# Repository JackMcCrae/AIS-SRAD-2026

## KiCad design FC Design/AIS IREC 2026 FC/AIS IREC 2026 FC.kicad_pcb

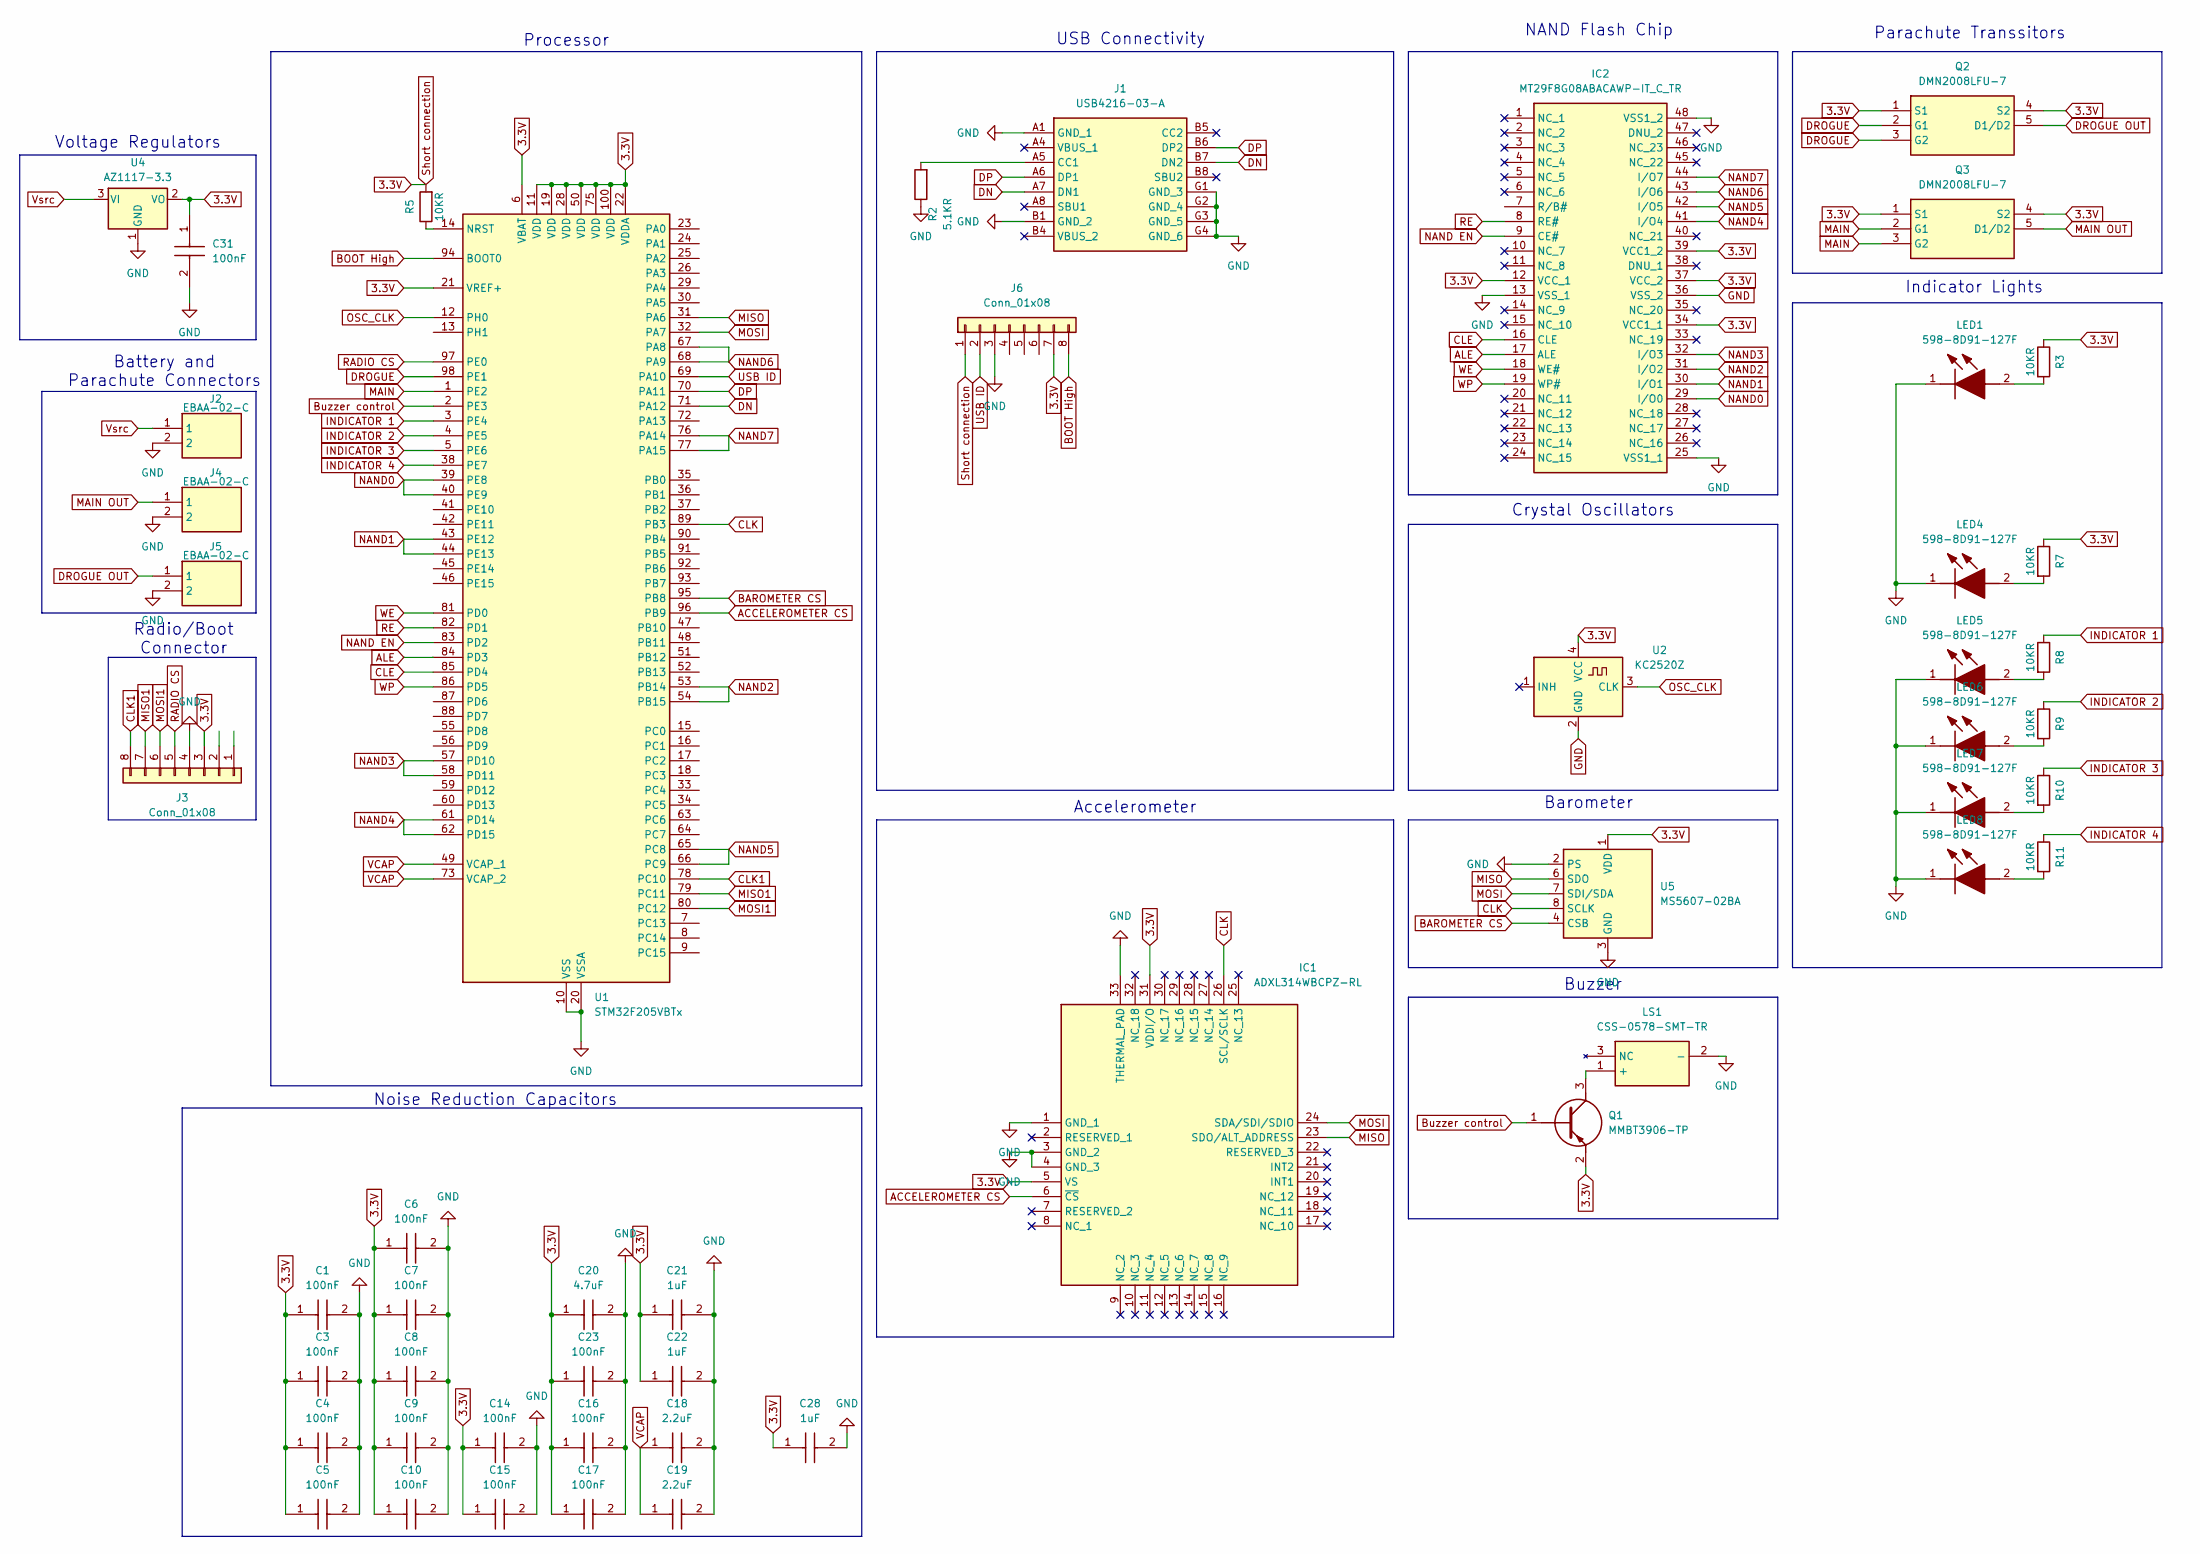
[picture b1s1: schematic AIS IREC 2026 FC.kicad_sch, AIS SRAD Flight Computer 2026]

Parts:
C1, C3, C4, C5, C6, C7, C8, C9, C10, C14, C15, C16, C17, C23, C31: 100nF; GRM022C81C222KE01L; Mouser Part Number 81-GRM022R61A104KE1L
C18, C19: 2.2uF; GRM033D70J224ME01D; Mouser Part Number 81-GRM033R61A225KE7D
C20: 4.7uF; GRM033D70J224ME01D; Mouser Part Number 81-GRM035R60J475ME5D
C21, C22, C28: 1uF; CAPC0603X33N; Mouser Part Number 81-GRT033R60J105ME3D
IC1: ADXL314WBCPZ-RL; QFN50P500X500X155-33N-D; Mouser Part Number 584-ADXL314WBCPZ-RL
IC2: MT29F8G08ABACAWP-IT_C_TR; SOP50P2000X120-48N; Mouser Part Number 340-122942-REEL
J1: USB4216-03-A; USB421603A; Mouser Part Number 640-USB4216-03-A
J2, J4, J5: EBAA-02-C; EBAA02C; Mouser Part Number 737-EBAA-02-C
J3, J6: Conn_01x08; Hirose_DF13-08P-1.25DSA_1x08_P1.25mm_Vertical
LED1, LED4, LED5, LED6, LED7, LED8: 598-8D91-127F; 5988D91127F; Manufacturer_Part_Number 598-8D91-127F
LS1: CSS-0578-SMT-TR; CSS0578SMTTR; Mouser Part Number 490-CSS-0578-SMT-TR
Q1: MMBT3906-TP; SOT95P237X125-3N; Mouser Part Number 833-MMBT3906-TP
Q2, Q3: DMN2008LFU-7; DMN2008LFU7; Mouser Part Number 621-DMN2008LFU-7
R2: 5.1KR; R_0201_0603Metric
R3, R5, R7, R8, R9, R10, R11: 10KR; R_0201_0603Metric
U1: STM32F205VBTx; LQFP-100_14x14mm_P0.5mm
U2: KC2520Z; Oscillator_SMD_Kyocera_KC2520Z-4Pin_2.5x2.0mm
U4: AZ1117-3.3; SOT-223-3_TabPin2
U5: MS5607-02BA; LGA-8_3x5mm_P1.25mm

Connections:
3.3V: C1.1, C3.1, C4.1, C5.1, C6.1, C7.1, C8.1, C9.1, C10.1, C14.1, C15.1, C16.1, C17.1, C20.1, C21.1, C22.1, C23.1, C28.1, C31.1, IC1.5 (VS), IC1.31 (VDDI/O), IC2.12 (VCC_1), IC2.34 (VCC1_1), IC2.37 (VCC_2), IC2.39 (VCC1_2), J3.3, J6.1, J6.7, Q1.2 (E), Q2.1 (S1), Q2.4 (S2), Q3.1 (S1), Q3.4 (S2), R3.1, R5.2, R7.1, U1.6 (VBAT), U1.11 (VDD), U1.19 (VDD), U1.21 (VREF+), U1.22 (VDDA), U1.28 (VDD), U1.50 (VDD), U1.75 (VDD), U1.100 (VDD), U2.4 (VCC), U4.2 (VO), U5.1 (VDD)
ACCELEROMETER CS: IC1.6 (~CS), U1.96 (PB9)
ALE: IC2.17 (ALE), U1.84 (PD3)
BAROMETER CS: U1.95 (PB8), U5.4 (CSB), U5.5 (CSB)
BOOT High: J6.8, U1.94 (BOOT0)
Buzzer control: Q1.1 (B), U1.2 (PE3)
CLE: IC2.16 (CLE), U1.85 (PD4)
CLK: IC1.26 (SCL/SCLK), U1.89 (PB3), U5.8 (SCLK)
CLK1: J3.8, U1.78 (PC10)
DN: J1.A7 (DN1), J1.B7 (DN2), U1.71 (PA12)
DP: J1.A6 (DP1), J1.B6 (DP2), U1.70 (PA11)
DROGUE: Q2.2 (G1), Q2.3 (G2), U1.98 (PE1)
DROGUE OUT: J5.1, Q2.5 (D1/D2)
GND: C1.2, C3.2, C4.2, C5.2, C6.2, C7.2, C8.2, C9.2, C10.2, C14.2, C15.2, C16.2, C17.2, C18.2, C19.2, C20.2, C21.2, C22.2, C23.2, C28.2, C31.2, IC1.1 (GND_1), IC1.3 (GND_2), IC1.4 (GND_3), IC1.33 (THERMAL_PAD), IC2.13 (VSS_1), IC2.25 (VSS1_1), IC2.36 (VSS_2), IC2.48 (VSS1_2), J1.A1 (GND_1), J1.B1 (GND_2), J1.G1 (GND_3), J1.G2 (GND_4), J1.G3 (GND_5), J1.G4 (GND_6), J2.2, J3.4, J4.2, J5.2, J6.3, LED1.1 (K), LED4.1 (K), LED5.1 (K), LED6.1 (K), LED7.1 (K), LED8.1 (K), LS1.2 (-), R2.1, U1.10 (VSS), U1.20 (VSSA), U1.27 (VSS), U1.74 (VSS), U2.2 (GND), U4.1 (GND), U5.2 (PS), U5.3 (GND)
INDICATOR 1: R8.1, U1.3 (PE4)
INDICATOR 2: R9.1, U1.4 (PE5)
INDICATOR 3: R10.1, U1.5 (PE6)
INDICATOR 4: R11.1, U1.38 (PE7)
MAIN: Q3.2 (G1), Q3.3 (G2), U1.1 (PE2)
MAIN OUT: J4.1, Q3.5 (D1/D2)
MISO: IC1.23 (SDO/ALT_ADDRESS), U1.31 (PA6), U5.6 (SDO)
MISO1: J3.7, U1.79 (PC11)
MOSI: IC1.24 (SDA/SDI/SDIO), U1.32 (PA7), U5.7 (SDI/SDA)
MOSI1: J3.6, U1.80 (PC12)
NAND0: IC2.29 (I/O0), U1.39 (PE8), U1.40 (PE9)
NAND1: IC2.30 (I/O1), U1.43 (PE12), U1.44 (PE13)
NAND2: IC2.31 (I/O2), U1.53 (PB14), U1.54 (PB15)
NAND3: IC2.32 (I/O3), U1.57 (PD10), U1.58 (PD11)
NAND4: IC2.41 (I/O4), U1.61 (PD14), U1.62 (PD15)
NAND5: IC2.42 (I/O5), U1.65 (PC8), U1.66 (PC9)
NAND6: IC2.43 (I/O6), U1.67 (PA8), U1.68 (PA9)
NAND7: IC2.44 (I/O7), U1.76 (PA14), U1.77 (PA15)
NAND EN: IC2.9 (CE#), U1.83 (PD2)
unnamed: J1.A5 (CC1), R2.2
unnamed: LED1.2 (A), R3.2
unnamed: LED4.2 (A), R7.2
unnamed: LED5.2 (A), R8.2
unnamed: LED6.2 (A), R9.2
unnamed: LED7.2 (A), R10.2
unnamed: LED8.2 (A), R11.2
unnamed: LS1.1 (+), Q1.3 (C)
unnamed: R5.1, U1.14 (NRST)
OSC_CLK: U1.12 (PH0), U2.3 (CLK)
RADIO CS: J3.5, U1.97 (PE0)
RE: IC2.8 (RE#), U1.82 (PD1)
USB ID: J6.2, U1.69 (PA10)
VCAP: C18.1, C19.1, U1.49 (VCAP_1), U1.73 (VCAP_2)
Vsrc: J2.1, U4.3 (VI)
WE: IC2.18 (WE#), U1.81 (PD0)
WP: IC2.19 (WP#), U1.86 (PD5)

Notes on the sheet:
Processor
Indicator Lights
Voltage Regulators
USB Connectivity
Battery and Parachute Connectors
Crystal Oscillators
Barometer
Noise Reduction Capacitors
Radio/Boot Connector
NAND Flash Chip
Buzzer
Accelerometer
Parachute Transsitors

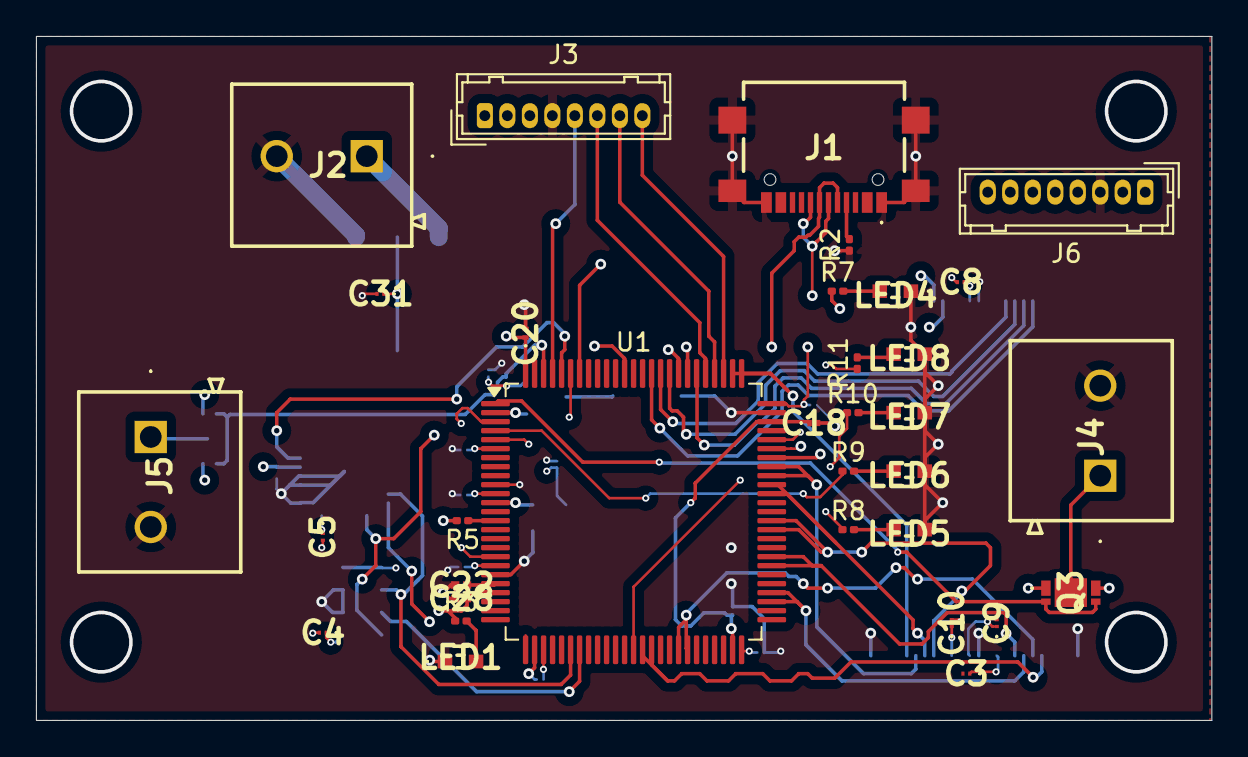
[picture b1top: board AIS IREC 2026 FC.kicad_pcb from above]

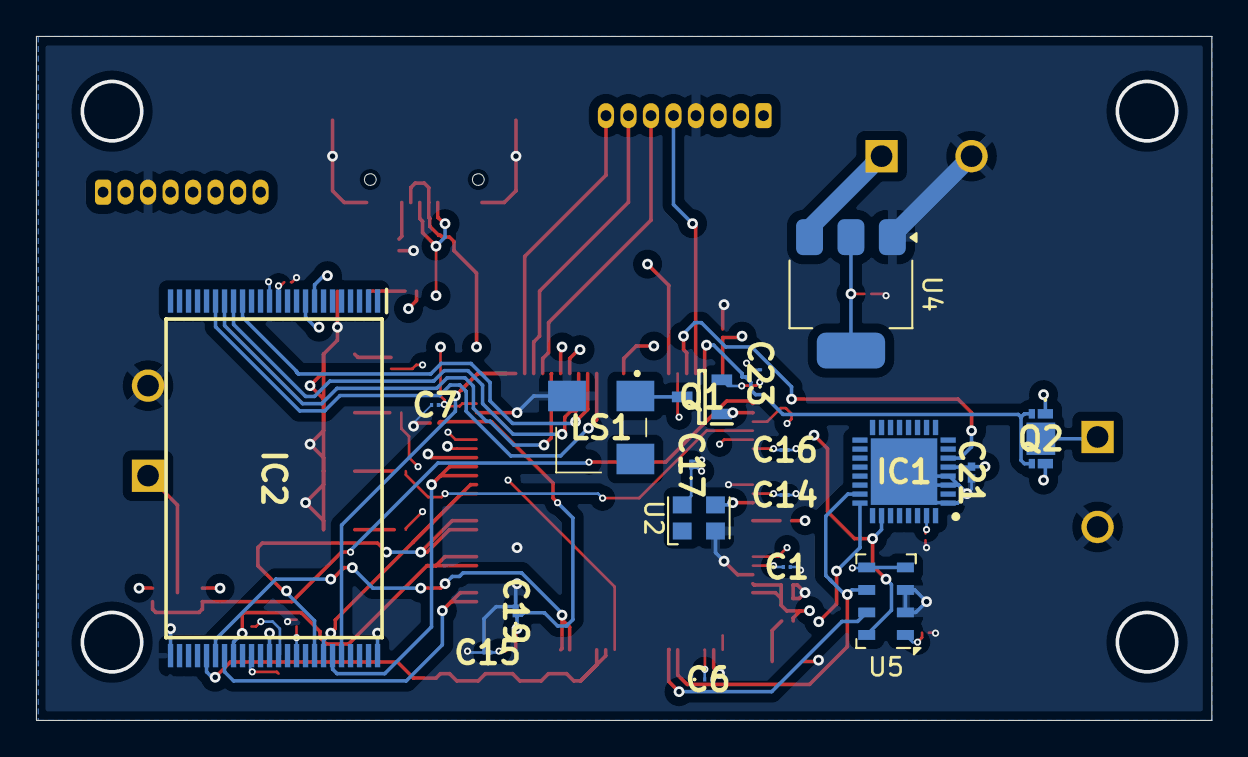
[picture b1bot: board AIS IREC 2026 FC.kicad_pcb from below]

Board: 4 copper layers, 65.3 x 38.0 mm, 51 parts (18 on the bottom side), 50 nets.

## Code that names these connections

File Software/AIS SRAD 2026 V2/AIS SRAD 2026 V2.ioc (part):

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Mcu.Name=STM32F205V(B-C-E-F-G)Tx
Mcu.Package=LQFP100
Mcu.UserName=STM32F205VBTx
PA10.Signal=GPIO_Input
PA11.Mode=Device_Only
PA11.Signal=USB_OTG_FS_DM
PA12.Mode=Device_Only
PA12.Signal=USB_OTG_FS_DP
PA14.Signal=GPIO_Output
PA15.Signal=GPIO_Input
PA3.Mode=OTG/Dual-Role-Device-HS
PA3.Signal=USB_OTG_HS_ULPI_D0
PA5.Mode=OTG/Dual-Role-Device-HS
PA5.Signal=USB_OTG_HS_ULPI_CK
PA6.Mode=Full_Duplex_Master
PA6.Signal=SPI1_MISO
PA7.Mode=Full_Duplex_Master
PA7.Signal=SPI1_MOSI
PA9.Signal=GPIO_Output
PB0.Mode=OTG/Dual-Role-Device-HS
PB0.Signal=USB_OTG_HS_ULPI_D1
PB1.Mode=OTG/Dual-Role-Device-HS
PB1.Signal=USB_OTG_HS_ULPI_D2
PB10.Mode=OTG/Dual-Role-Device-HS
PB10.Signal=USB_OTG_HS_ULPI_D3
PB11.Mode=OTG/Dual-Role-Device-HS
PB11.Signal=USB_OTG_HS_ULPI_D4
PB12.Mode=OTG/Dual-Role-Device-HS
PB12.Signal=USB_OTG_HS_ULPI_D5
PB13.Mode=OTG/Dual-Role-Device-HS
PB13.Signal=USB_OTG_HS_ULPI_D6
PB14.Signal=GPIO_Output
PB15.Signal=GPIO_Input
PB3.Mode=Full_Duplex_Master
PB3.Signal=SPI1_SCK
PB5.Mode=OTG/Dual-Role-Device-HS
PB5.Signal=USB_OTG_HS_ULPI_D7
PB8.Signal=GPIO_Output
PB9.Signal=GPIO_Output
PC0.Mode=OTG/Dual-Role-Device-HS
PC0.Signal=USB_OTG_HS_ULPI_STP
PC10.Mode=Full_Duplex_Master
PC10.Signal=SPI3_SCK
PC11.Mode=Full_Duplex_Master
PC11.Signal=SPI3_MISO
PC12.Mode=Full_Duplex_Master
PC12.Signal=SPI3_MOSI
PC14-OSC32_IN.Signal=GPXTI14
PC2.Mode=OTG/Dual-Role-Device-HS
PC2.Signal=USB_OTG_HS_ULPI_DIR
PC3.Mode=OTG/Dual-Role-Device-HS
PC3.Signal=USB_OTG_HS_ULPI_NXT
PC8.Signal=GPIO_Output
PC9.Signal=GPIO_Input
PD0.Signal=GPXTI0
PD1.Signal=GPIO_Output
PD10.Signal=GPIO_Output
PD11.Signal=GPIO_Input
PD14.Signal=GPIO_Output
PD15.Signal=GPIO_Input
PD2.Signal=GPIO_Output
PD3.Signal=GPIO_Output
PD4.Signal=GPIO_Output
PD5.Signal=GPIO_Output
PE0.Signal=GPIO_Output
PE12.Signal=GPIO_Output
PE13.Signal=GPIO_Input
PE2.Signal=GPIO_Output
PE3.Signal=GPIO_Output
PE4.Signal=GPIO_Output
PE8.Signal=GPIO_Output
PE9.Signal=GPIO_Input
PH0-OSC_IN.Mode=HSE-External-Clock-Source
PH0-OSC_IN.Signal=RCC_OSC_IN
PH1-OSC_OUT.Mode=HSE-External-Clock-Source
PH1-OSC_OUT.Signal=RCC_OSC_OUT
RCC.HSE_VALUE=12000000
RCC.SYSCLKFreq_VALUE=96000000
RCC.SYSCLKSource=RCC_SYSCLKSOURCE_PLLCLK
board=custom

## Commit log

2026-01-11 Files generated by STM32 cube IDE & pcb schematic before pcb design is started
2026-01-14 Added transistors to schematic
2026-01-16 Altered FC design and setup on Cube IDE for flashing
2026-01-16 Updates to wiring to help with flashing of microprocessor
2026-01-16 Component placement done for pcb
2026-01-16 Updated details on pcb
2026-01-18 Updates to pcb
2026-01-18 Added datasheets for components to github
2026-01-21 More changes
2026-01-25 Readability changes
2026-01-31 added ESRA discord flight data
2026-01-31 added ras aero flight simulation
2026-01-31 more predicted flight data
2026-01-31 added unit conversions
2026-02-25 Don't know what changed
    Beans
2026-02-25 Add files via upload
    Main control in C++
2026-02-27 Added PCB layout
    Layout is 48% smaller than AV bay was designed to hold, so no issues, space left because I'm lazy. Allows for further improvement in subsequent years.
2026-02-27 Fucking hell
    All of the routing. All of the fucking routing.
2026-03-04 Implement Kalman filter for altitude measurement
2026-03-10 PCB routing changes
2026-03-11 Changed from usb fs and hs to just usb fs, made appropriate changes
2026-03-11 Got PCB to a state where I'm happy for Logan to look at it before manufacture
2026-03-23 Generated gerber and drill files for pcb
2026-03-24 updated gerbers, BOM and placement files + component changes based off of JLC part availability
2026-03-25 Further PCB changes. Mainly BOM, gerbers and PLC
2026-04-09 Create NANDflash
2026-05-22 Intergrated NAND flash into flight_main
    As well as improvements in kalman filter, but not done yet
2026-05-22 Accelerometer & Barometer
